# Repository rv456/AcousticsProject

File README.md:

# AcousticsProject
---------------

Acoustics and Audio Technology 4 loudspeaker project repository.

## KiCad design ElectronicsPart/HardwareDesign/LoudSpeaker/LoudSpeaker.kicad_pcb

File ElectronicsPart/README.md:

# Electronics Part
---------

This folder contains the files used to derive the electronic system as detailed in the final report.

## Resources

Contains the BOM of the system, and a spreadsheet for calculating model parameters.

## HardwareDesign

Contains the real component valued schematic corresponding PCB design.

## Simulation

Contains the LTSpice simulation files used to model the system, and plots of various outputs that were used in the final report.

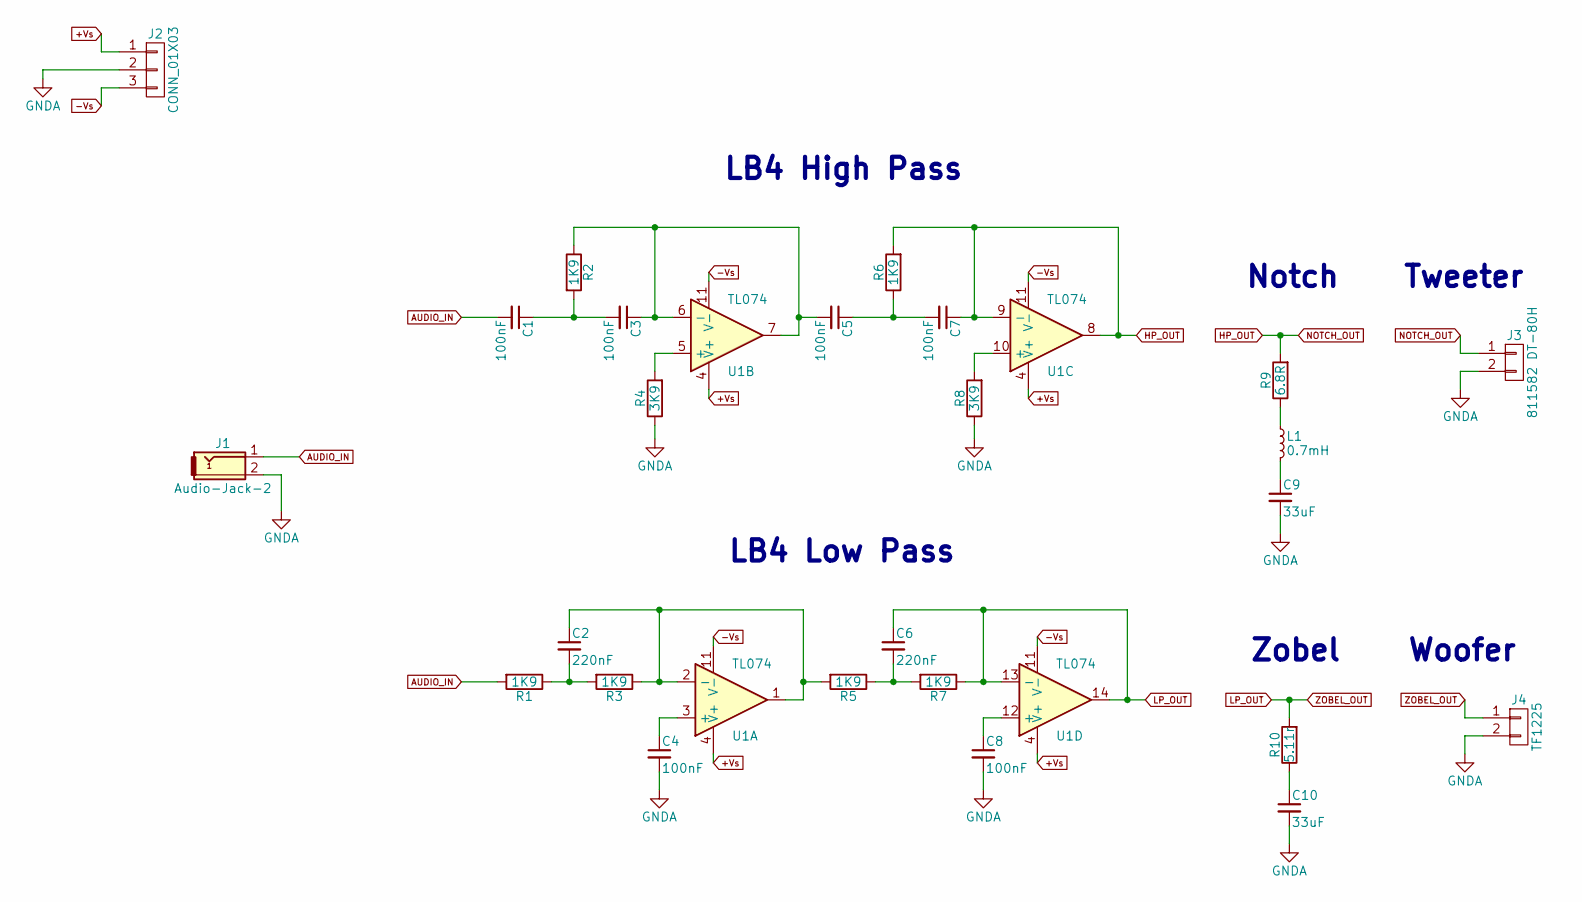
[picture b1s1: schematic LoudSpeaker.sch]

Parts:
C1, C3, C4, C5, C7, C8: 100nF; C_Rect_L10.0mm_W4.0mm_P7.50mm_FKS3_FKP3; mouser# 80-SMR5104J50J0116
C2, C6: 220nF; C_Rect_L10.0mm_W4.0mm_P7.50mm_FKS3_FKP3; mouser# 80-SMR5224J50J0216
C9, C10: 33uF; CP_Radial_D12.5mm_P5.00mm; mouser# 647-UKZ1H330MPM
J1: Audio-Jack-2; BARREL_JACK; mouser# 490-RCJ-042
J2: CONN_01X03; TerminalBlock_Altech_AK300-3_P5.00mm
J3: 811582 DT-80H; TerminalBlock_Altech_AK300-2_P5.00mm; mouser# NA
J4: TF1225; TerminalBlock_Altech_AK300-2_P5.00mm; mouser# NA
L1: 0.7mH; L_Radial_D12.0mm_P5.00mm_Fastron_11P; mouser# 434-11PHC-701K
R1, R2, R3, R5, R6, R7: 1K9; R_Axial_DIN0207_L6.3mm_D2.5mm_P10.16mm_Horizontal; mouser# 594-5063JD1K910FT
R4, R8: 3K9; R_Axial_DIN0207_L6.3mm_D2.5mm_P10.16mm_Horizontal; mouser# 594-5063JD3K900F
R9: 6.8R; R_Axial_DIN0207_L6.3mm_D2.5mm_P10.16mm_Horizontal; mouser# 594-5063JD6R800F5
R10: 5.11r; R_Axial_DIN0207_L6.3mm_D2.5mm_P10.16mm_Horizontal; mouser# 594-5063JD5R110F
U1: TL074; DIP-14_W7.62mm_LongPads; mouser# 595-TL074CN

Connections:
+Vs: J2.1, U1.4 (V+)
-Vs: J2.3, U1.11 (V-)
AUDIO_IN: C1.2, J1.1, R1.2
GNDA: C4.2, C8.2, C9.2, C10.2, J1.2, J2.2, J3.2, J4.2, R4.1, R8.1
HP_OUT: C7.1, J3.1, R6.2, R9.2, U1.8, U1.9 (-)
LP_OUT: C6.1, J4.1, R7.1, R10.2, U1.13 (-), U1.14
unnamed: C1.1, C3.2, R2.2
unnamed: C2.1, R3.1, R5.2, U1.1, U1.2 (-)
unnamed: C2.2, R1.1, R3.2
unnamed: C3.1, C5.2, R2.1, U1.6 (-), U1.7
unnamed: C4.1, U1.3 (+)
unnamed: C5.1, C7.2, R6.1
unnamed: C6.2, R5.1, R7.2
unnamed: C8.1, U1.12 (+)
unnamed: C9.1, L1.2
unnamed: C10.1, R10.1
unnamed: L1.1, R9.1
unnamed: R4.2, U1.5 (+)
unnamed: R8.2, U1.10 (+)

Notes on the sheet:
Tweeter
Woofer
Zobel
Notch
LB4 High Pass
LB4 Low Pass

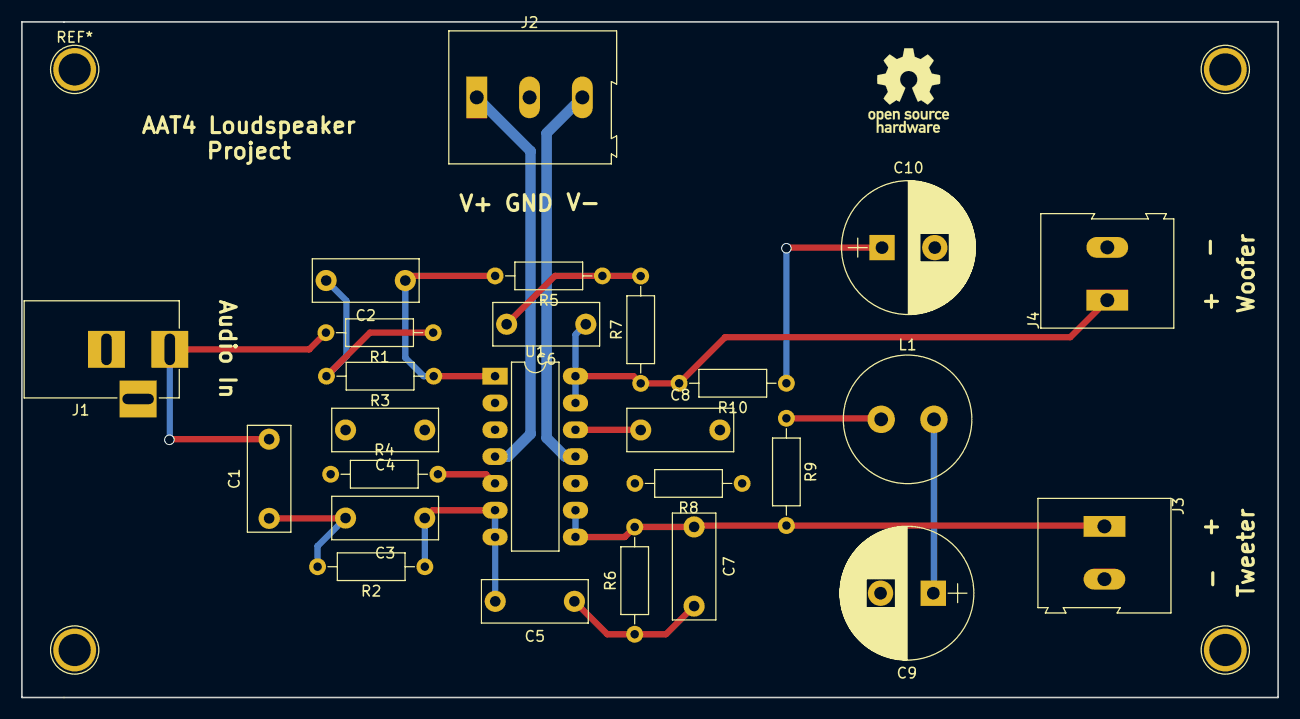
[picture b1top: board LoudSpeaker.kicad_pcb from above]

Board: 2 copper layers, 119.0 x 64.0 mm, 26 parts (0 on the bottom side), 19 nets.

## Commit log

2018-03-20 Added some resources
2018-03-20 added more resources
2018-03-20 links.txt
2018-03-25 added transducer free space sims and calculation spreadsheet
2018-03-25 added zobel and notch simulations
2018-03-25 updated model calculation spreadsheet
2018-04-11 Added electronics part
2018-04-25 modified links
2018-05-05 putting report in folder
